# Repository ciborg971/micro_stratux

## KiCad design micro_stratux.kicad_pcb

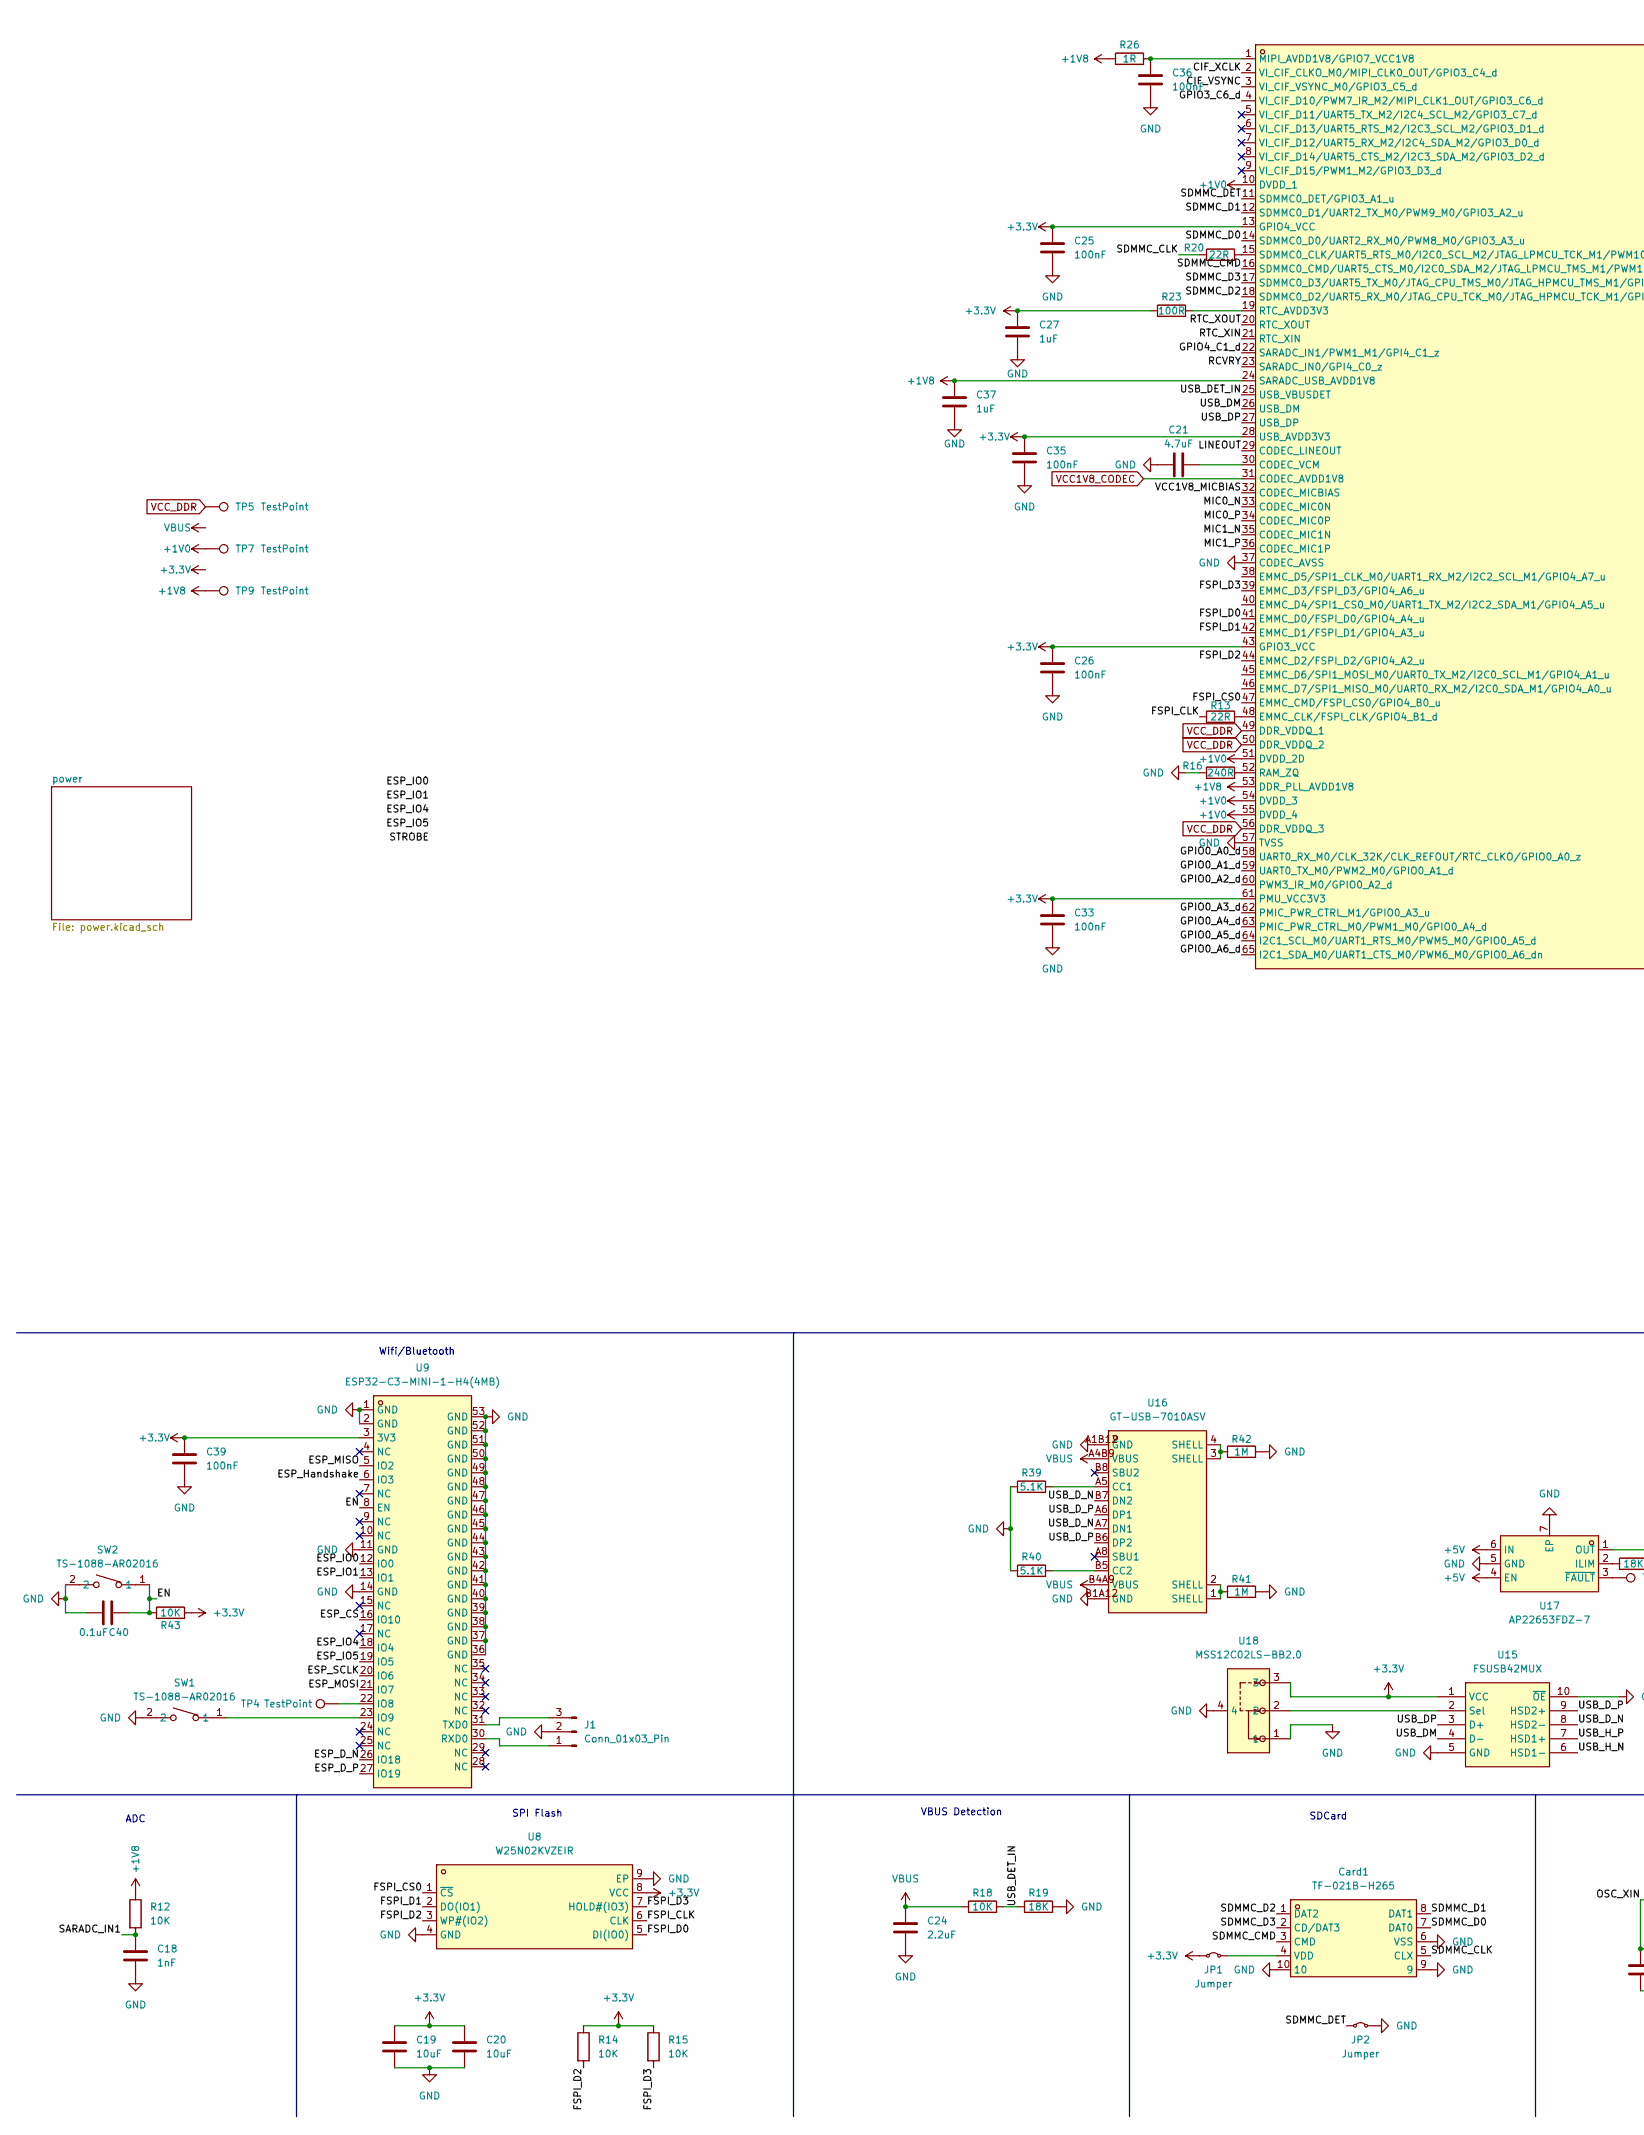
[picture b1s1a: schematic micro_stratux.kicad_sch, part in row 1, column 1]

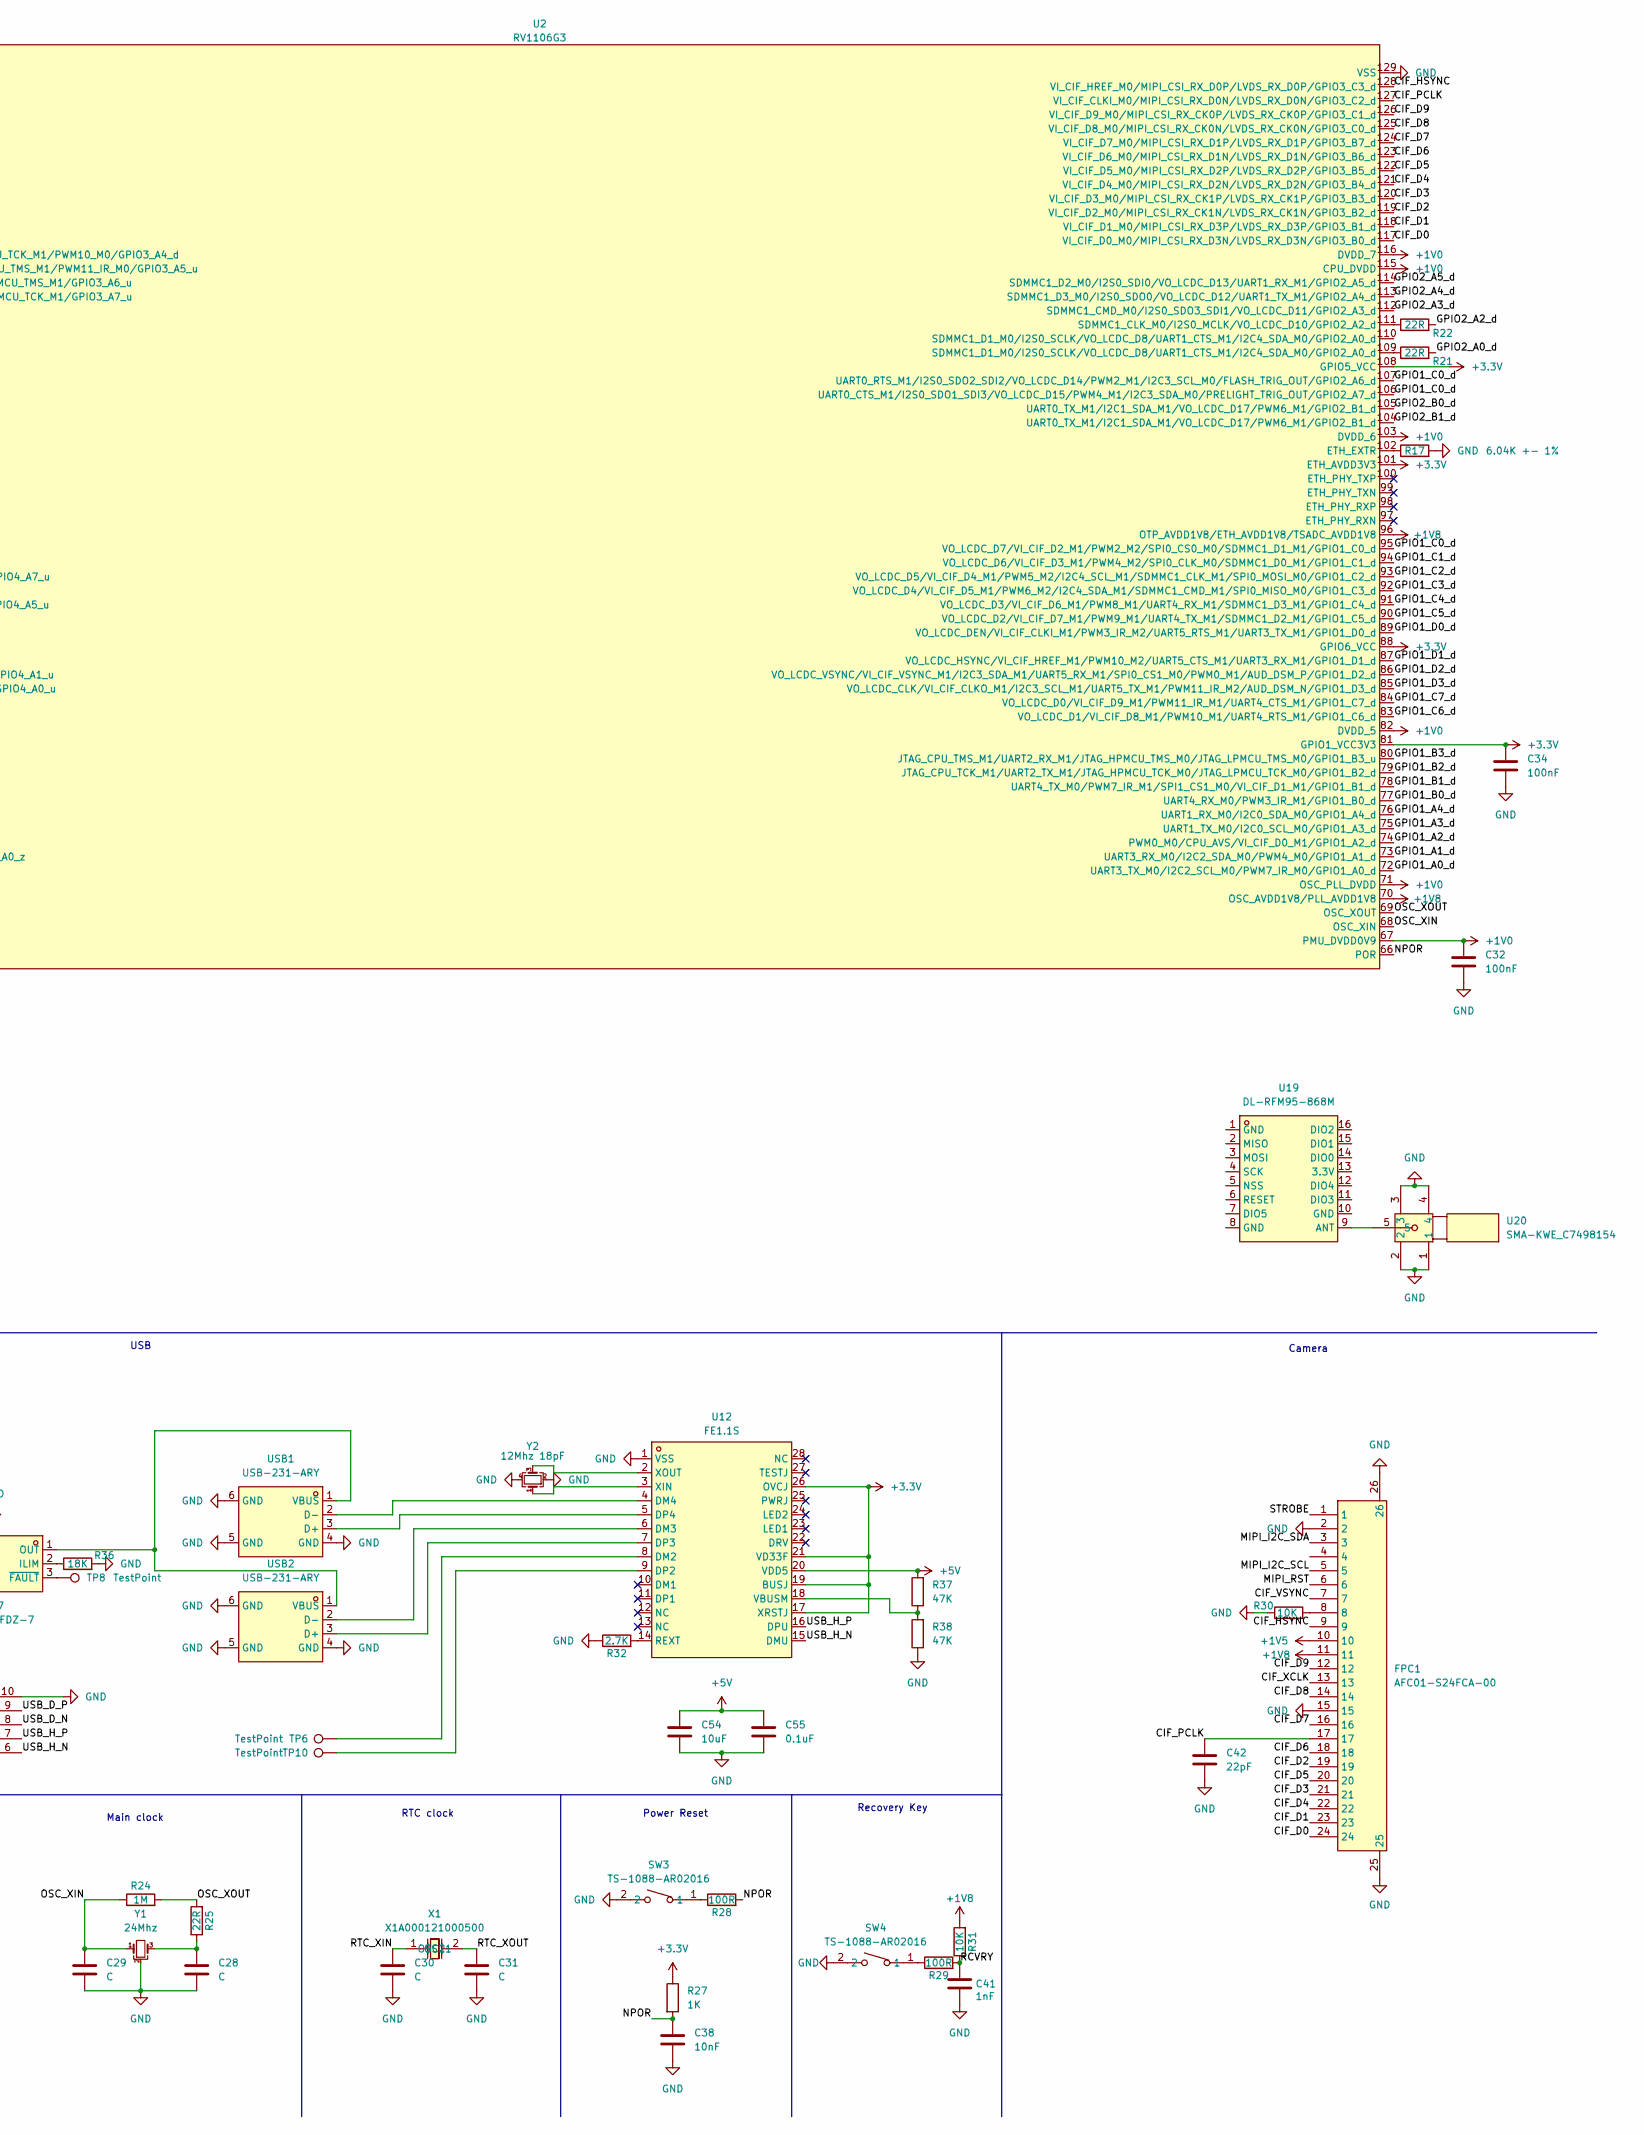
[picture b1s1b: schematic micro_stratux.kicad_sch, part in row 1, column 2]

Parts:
C18, C41: 1nF; C_0402_1005Metric
C19, C20, C54: 10uF; C_0805_2012Metric
C21: 4.7uF; C_0805_2012Metric
C24: 2.2uF; C_0402_1005Metric
C25, C26, C32, C33, C34, C35, C36, C39: 100nF; C_0402_1005Metric
C27, C37: 1uF; C_0402_1005Metric
C28, C29, C30, C31: C; C_0201_0603Metric
C38: 10nF; C_0402_1005Metric
C40, C55: 0.1uF; C_0402_1005Metric
C42: 22pF; C_0201_0603Metric
Card1: TF-021B-H265; TF-SMD_TF-021B-H265; LCSC Part C498185
FPC1: AFC01-S24FCA-00; FPC-SMD_P0.50-24P_FGS-XJ-H2.0; LCSC Part C262669
J1: Conn_01x03_Pin
JP1, JP2: Jumper; TestPoint_2Pads_Pitch2.54mm_Drill0.8mm
R12, R14, R15, R18, R30, R31, R43: 10K; R_0201_0603Metric
R13, R20, R21, R22, R25: 22R; R_0201_0603Metric
R16: 240R; R_0201_0603Metric
R17: 6.04K +- 1%; R_0201_0603Metric
R19: 18K; R_0201_0603Metric
R23, R28, R29: 100R; R_0201_0603Metric
R24, R41, R42: 1M; R_0201_0603Metric
R26: 1R; R_0201_0603Metric
R27: 1K; R_0201_0603Metric
R32: 2.7K; R_0201_0603Metric
R36: 18K; R_0402_1005Metric
R37, R38: 47K; R_0201_0603Metric
R39, R40: 5.1K; R_0201_0603Metric
SW1, SW2, SW3, SW4: TS-1088-AR02016; SW-SMD_L3.9-W3.0-P4.45; LCSC Part C720477
TP4, TP5, TP6, TP7, TP8, TP9, TP10: TestPoint; TestPoint_Pad_D1.0mm
U2: RV1106G3; QFN-128_L12.3-W12.3-P0.35-TL-EP7.0-1; LCSC Part C5328706
U8: W25N02KVZEIR; WSON-8_L8.0-W6.0-P1.27-TL-EP-1; LCSC Part C3010298
U9: ESP32-C3-MINI-1-H4(4MB); WIFIM-SMD_ESP32-C3-MINI-1; LCSC Part C2934569
U12: FE1.1S; SSOP-28_L9.9-W3.9-P0.64-LS6.0-BL-1; LCSC Part C9359
U15: FSUSB42MUX; MSOP-10_L3.0-W3.0-P0.50-LS5.0-BL; LCSC Part C11355
U16: GT-USB-7010ASV; USB-C-SMD_G-SWITCH_GT-USB-7010ASV; LCSC Part C2988369
U17: AP22653FDZ-7; WDFN-6_L2.0-W2.0-P0.65-BL-EP; LCSC Part C3001604
U18: MSS12C02LS-BB2.0; SW-SMD_MSS12C02LS-HB2.0-1; LCSC Part C3008585
U19: DL-RFM95-868M; COMM-SMD_RFM95W; LCSC Part C2844472
U20: SMA-KWE_C7498154; SMA-TH_SMA-KWE_C7498154; LCSC Part C7498154
USB1, USB2: USB-231-ARY; USB-A-TH_USB-231-ARY; LCSC Part C720525
X1: X1A000121000500; CRYSTAL-SMD_L1.7-W1.1; LCSC Part C5154201
Y1: 24Mhz; Crystal_SMD_2016-4Pin_2.0x1.6mm; LCSC C2929397
Y2: 12Mhz 18pF; Crystal_SMD_2520-4Pin_2.5x2.0mm; LCSC C2149207

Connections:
+1V0: C32.1, TP7.1, U2.10 (DVDD_1), U2.51 (DVDD_2D), U2.54 (DVDD_3), U2.55 (DVDD_4), U2.67 (PMU_DVDD0V9), U2.71 (OSC_PLL_DVDD), U2.82 (DVDD_5), U2.103 (DVDD_6), U2.115 (CPU_DVDD), U2.116 (DVDD_7); also elsewhere on the board
+1V5: FPC1.10; also elsewhere on the board
+1V8: C37.1, FPC1.11, R12.1, R26.1, R31.2, TP9.1, U2.24 (SARADC_USB_AVDD1V8), U2.53 (DDR_PLL_AVDD1V8), U2.70 (OSC_AVDD1V8/PLL_AVDD1V8), U2.96 (OTP_AVDD1V8/ETH_AVDD1V8/TSADC_AVDD1V8); also elsewhere on the board
+3.3V: C19.1, C20.1, C25.1, C26.1, C27.1, C33.1, C34.1, C35.1, C39.1, JP1.1 (A), R14.1, R15.1, R23.1, R27.1, R43.2, U2.13 (GPIO4_VCC), U2.28 (USB_AVDD3V3), U2.43 (GPIO3_VCC), U2.61 (PMU_VCC3V3), U2.81 (GPIO1_VCC3V3), U2.88 (GPIO6_VCC), U2.101 (ETH_AVDD3V3), U2.108 (GPIO5_VCC), U8.8 (VCC), U9.3 (3V3), U12.17 (XRSTJ), U12.19 (BUSJ), U12.21 (VD33F), U12.26 (OVCJ), U15.1 (VCC), U18.3; also elsewhere on the board
+5V: C54.1, C55.1, R37.2, U12.20 (VDD5), U17.4 (EN), U17.6 (IN); also elsewhere on the board
/CIF_D0: FPC1.24, U2.117 (VI_CIF_D0_M0/MIPI_CSI_RX_D3N/LVDS_RX_D3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)
/CIF_D1: FPC1.23, U2.118 (VI_CIF_D1_M0/MIPI_CSI_RX_D3P/LVDS_RX_D3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)
/CIF_D2: FPC1.19, U2.119 (VI_CIF_D2_M0/MIPI_CSI_RX_CK1N/LVDS_RX_C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)
/CIF_D3: FPC1.21, U2.120 (VI_CIF_D3_M0/MIPI_CSI_RX_CK1P/LVDS_RX_C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)
/CIF_D4: FPC1.22, U2.121 (VI_CIF_D4_M0/MIPI_CSI_RX_D2N/LVDS_RX_D2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)
/CIF_D5: FPC1.20, U2.122 (VI_CIF_D5_M0/MIPI_CSI_RX_D2P/LVDS_RX_D2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)
/CIF_D6: FPC1.18, U2.123 (VI_CIF_D6_M0/MIPI_CSI_RX_D1N/LVDS_RX_D1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)
/CIF_D7: FPC1.16, U2.124 (VI_CIF_D7_M0/MIPI_CSI_RX_D1P/LVDS_RX_D1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)
/CIF_D8: FPC1.14, U2.125 (VI_CIF_D8_M0/MIPI_CSI_RX_CK0N/LVDS_RX_C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)
/CIF_D9: FPC1.12, U2.126 (VI_CIF_D9_M0/MIPI_CSI_RX_CK0P/LVDS_RX_C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)
/CIF_HSYNC: FPC1.9, U2.128 (VI_CIF_HREF_M0/MIPI_CSI_RX_D0P/LVDS_RX_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)
/CIF_PCLK: C42.1, FPC1.17, U2.127 (VI_CIF_CLKI_M0/MIPI_CSI_RX_D0N/LVDS_RX_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)
/CIF_VSYNC: FPC1.7, U2.3 (VI_CIF_VSYNC_M0/GPIO3_C5_d)
/CIF_XCLK: FPC1.13, U2.2 (VI_CIF_CLKO_M0/MIPI_CLK0_OUT/GPIO3_C4_d)
/EN: C40.2, R43.1, SW2.1, U9.8 (EN)
/ESP_CS: U9.16 (IO10)
/ESP_D_N: U9.26 (IO18)
/ESP_D_P: U9.27 (IO19)
/ESP_Handshake: U9.6 (IO3)
/ESP_IO0: U9.12 (IO0)
/ESP_IO1: U9.13 (IO1)
/ESP_IO4: U9.18 (IO4)
/ESP_IO5: U9.19 (IO5)
/ESP_MISO: U9.5 (IO2)
/ESP_MOSI: U9.21 (IO7)
/ESP_SCLK: U9.20 (IO6)
/FSPI_CLK: R13.1, U8.6 (CLK)
/FSPI_CS0: U2.47 (EMMC_CMD/FSPI_CS0/GPIO4_B0_u), U8.1 (~CS)
/FSPI_D0: U2.41 (EMMC_D0/FSPI_D0/GPIO4_A4_u), U8.5 (DI(IO0))
/FSPI_D1: U2.42 (EMMC_D1/FSPI_D1/GPIO4_A3_u), U8.2 (DO(IO1))
/FSPI_D2: R14.2, U2.44 (EMMC_D2/FSPI_D2/GPIO4_A2_u), U8.3 (WP#(IO2))
/FSPI_D3: R15.2, U2.39 (EMMC_D3/FSPI_D3/GPIO4_A6_u), U8.7 (HOLD#(IO3))
/GPIO0_A0_d: U2.58 (UART0_RX_M0/CLK_32K/CLK_REFOUT/RTC_CLKO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)
/GPIO0_A1_d: U2.59 (UART0_TX_M0/PWM2_M0/GPIO0_A1_d)
/GPIO0_A2_d: U2.60 (PWM3_IR_M0/GPIO0_A2_d)
/GPIO0_A3_d: U2.62 (PMIC_PWR_CTRL_M1/GPIO0_A3_u)
/GPIO0_A4_d: U2.63 (PMIC_PWR_CTRL_M0/PWM1_M0/GPIO0_A4_d)
/GPIO0_A5_d: U2.64 (I2C1_SCL_M0/UART1_RTS_M0/PWM5_M0/GPIO0_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)
/GPIO0_A6_d: U2.65 (I2C1_SDA_M0/UART1_CTS_M0/PWM6_M0/GPIO0_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)
/GPIO1_A0_d: U2.72 (UART3_TX_M0/I2C2_SCL_M0/PWM7_IR_M0/GPIO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)
/GPIO1_A1_d: U2.73 (UART3_RX_M0/I2C2_SDA_M0/PWM4_M0/GPIO1_A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)
/GPIO1_A2_d: U2.74 (PWM0_M0/CPU_AVS/VI_CIF_D0_M1/GPIO1_A2_d)
/GPIO1_A3_d: U2.75 (UART1_TX_M0/I2C0_SCL_M0/GPIO1_A3_d)
/GPIO1_A4_d: U2.76 (UART1_RX_M0/I2C0_SDA_M0/GPIO1_A4_d)
/GPIO1_B0_d: U2.77 (UART4_RX_M0/PWM3_IR_M1/GPIO1_B0_d)
/GPIO1_B1_d: U2.78 (UART4_TX_M0/PWM7_IR_M1/SPI1_CS1_M0/VI_C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)
/GPIO1_B2_d: U2.79 (JTAG_CPU_TCK_M1/UART2_TX_M1/JTAG_HPMCU_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)
/GPIO1_B3_d: U2.80 (JTAG_CPU_TMS_M1/UART2_RX_M1/JTAG_HPMCU_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)
/GPIO1_C0_d: U2.95 (VO_LCDC_D7/VI_CIF_D2_M1/PWM2_M2/SPI0_CS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), U2.106 (UART0_CTS_M1/I2S0_SDO1_SDI3/VO_LCDC_D15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), U2.107 (UART0_RTS_M1/I2S0_SDO2_SDI2/VO_LCDC_D14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)
/GPIO1_C1_d: U2.94 (VO_LCDC_D6/VI_CIF_D3_M1/PWM4_M2/SPI0_CL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)
/GPIO1_C2_d: U2.93 (VO_LCDC_D5/VI_CIF_D4_M1/PWM5_M2/I2C4_SC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)
/GPIO1_C3_d: U2.92 (VO_LCDC_D4/VI_CIF_D5_M1/PWM6_M2/I2C4_SD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)
/GPIO1_C4_d: U2.91 (VO_LCDC_D3/VI_CIF_D6_M1/PWM8_M1/UART4_R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)
/GPIO1_C5_d: U2.90 (VO_LCDC_D2/VI_CIF_D7_M1/PWM9_M1/UART4_T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)
/GPIO1_C6_d: U2.83 (VO_LCDC_D1/VI_CIF_D8_M1/PWM10_M1/UART4_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)
/GPIO1_C7_d: U2.84 (VO_LCDC_D0/VI_CIF_D9_M1/PWM11_IR_M1/UAR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)
/GPIO1_D0_d: U2.89 (VO_LCDC_DEN/VI_CIF_CLKI_M1/PWM3_IR_M2/U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)
/GPIO1_D1_d: U2.87 (VO_LCDC_HSYNC/VI_CIF_HREF_M1/PWM10_M2/U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)
/GPIO1_D2_d: U2.86 (VO_LCDC_VSYNC/VI_CIF_VSYNC_M1/I2C3_SDA_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)
/GPIO1_D3_d: U2.85 (VO_LCDC_CLK/VI_CIF_CLKO_M1/I2C3_SCL_M1/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)
/GPIO2_A0_d: R21.2
/GPIO2_A2_d: R22.2
/GPIO2_A3_d: U2.112 (SDMMC1_CMD_M0/I2S0_SDO3_SDI1/VO_LCDC_D1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)
/GPIO2_A4_d: U2.113 (SDMMC1_D3_M0/I2S0_SDO0/VO_LCDC_D12/UART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)
/GPIO2_A5_d: U2.114 (SDMMC1_D2_M0/I2S0_SDI0/VO_LCDC_D13/UART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)
/GPIO2_B0_d: U2.105 (UART0_TX_M1/I2C1_SDA_M1/VO_LCDC_D17/PWM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)
/GPIO2_B1_d: U2.104 (UART0_TX_M1/I2C1_SDA_M1/VO_LCDC_D17/PWM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)
/GPIO3_C6_d: U2.4 (VI_CIF_D10/PWM7_IR_M2/MIPI_CLK1_OUT/GPI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)
/GPIO4_C1_d: U2.22 (SARADC_IN1/PWM1_M1/GPI4_C1_z)
/LINEOUT: U2.29 (CODEC_LINEOUT)
/MIC0_N: U2.33 (CODEC_MIC0N)
/MIC0_P: U2.34 (CODEC_MIC0P)
/MIC1_N: U2.35 (CODEC_MIC1N)
/MIC1_P: U2.36 (CODEC_MIC1P)
/MIPI_I2C_SCL: FPC1.5
/MIPI_I2C_SDA: FPC1.3
/MIPI_RST: FPC1.6
/NPOR: C38.1, R27.2, R28.2, U2.66 (POR)
/OSC_XIN: C29.1, R24.1, U2.68 (OSC_XIN), Y1.1
/OSC_XOUT: R24.2, R25.2, U2.69 (OSC_XOUT)
/RCVRY: C41.1, R29.2, R31.1, U2.23 (SARADC_IN0/GPI4_C0_z)
/RTC_XIN: C30.1, U2.21 (RTC_XIN), X1.1 (OSC1)
/RTC_XOUT: C31.1, U2.20 (RTC_XOUT), X1.2 (OSC2)
/SARADC_IN1: C18.1, R12.2
/SDMMC_CLK: Card1.5 (CLX), R20.1
/SDMMC_CMD: Card1.3 (CMD), U2.16 (SDMMC0_CMD/UART5_CTS_M0/I2C0_SDA_M2/JTA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)
/SDMMC_D0: Card1.7 (DAT0), U2.14 (SDMMC0_D0/UART2_RX_M0/PWM8_M0/GPIO3_A3_u)
/SDMMC_D1: Card1.8 (DAT1), U2.12 (SDMMC0_D1/UART2_TX_M0/PWM9_M0/GPIO3_A2_u)
/SDMMC_D2: Card1.1 (DAT2), U2.18 (SDMMC0_D2/UART5_RX_M0/JTAG_CPU_TCK_M0/J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)
/SDMMC_D3: Card1.2 (CD/DAT3), U2.17 (SDMMC0_D3/UART5_TX_M0/JTAG_CPU_TMS_M0/J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)
/SDMMC_DET: JP2.1 (A), U2.11 (SDMMC0_DET/GPIO3_A1_u)
/STROBE: FPC1.1
/USB_DET_IN: R18.2, R19.1, U2.25 (USB_VBUSDET)
/USB_DM: U2.26 (USB_DM), U15.4 (D-)
/USB_DP: U2.27 (USB_DP), U15.3 (D+)
/USB_D_N: U15.8 (HSD2-), U16.A7 (DN1), U16.B7 (DN2)
/USB_D_P: U15.9 (HSD2+), U16.A6 (DP1), U16.B6 (DP2)
/USB_H_N: U12.15 (DMU), U15.6 (HSD1-)
/USB_H_P: U12.16 (DPU), U15.7 (HSD1+)
/VCC1V8_MICBIAS: U2.32 (CODEC_MICBIAS)
GND: C18.2, C19.2, C20.2, C21.1, C24.2, C25.2, C26.2, C27.2, C28.2, C29.2, C30.2, C31.2, C32.2, C33.2, C34.2, C35.2, C36.2, C37.2, C38.2, C39.2, C40.1, C41.2, C42.2, C54.2, C55.2, Card1.6 (VSS), Card1.9, Card1.10, FPC1.2, FPC1.15, FPC1.25, FPC1.26, J1.2, JP2.2 (B), R16.1, R17.2, R19.2, R30.1, R32.1, R36.2, R38.1, R39.1, R40.1, R41.2, R42.2, SW1.2, SW2.2, SW3.2, SW4.2, U2.37 (CODEC_AVSS), U2.57 (TVSS), U2.129 (VSS), U8.4 (GND), U8.9 (EP), U9.1 (GND), U9.2 (GND), U9.11 (GND), U9.14 (GND), U9.36 (GND), U9.37 (GND), U9.38 (GND), U9.39 (GND), U9.40 (GND), U9.41 (GND), U9.42 (GND), U9.43 (GND), U9.44 (GND), U9.45 (GND), U9.46 (GND), U9.47 (GND), U9.48 (GND), U9.49 (GND), U9.50 (GND), U9.51 (GND), U9.52 (GND), U9.53 (GND), U12.1 (VSS), U15.5 (GND), U15.10 (~OE), U16.A1B12 (GND), U16.B1A12 (GND), U17.5 (GND), U17.7 (EP), U18.1, U18.4, U20.1, U20.2, U20.3, U20.4, USB1.4 (GND), USB1.5 (GND), USB1.6 (GND), USB2.4 (GND), USB2.5 (GND), USB2.6 (GND), Y1.2, Y2.2, Y2.4; also elsewhere on the board
unnamed: C28.1, R25.1, Y1.3
unnamed: Card1.4 (VDD), JP1.2 (B)
unnamed: FPC1.8, R30.2
unnamed: J1.1, U9.30 (RXD0)
unnamed: J1.3, U9.31 (TXD0)
unnamed: R21.1, U2.109 (SDMMC1_D1_M0/I2S0_SCLK/VO_LCDC_D8/UART1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)
unnamed: R28.1, SW3.1
unnamed: R29.1, SW4.1
unnamed: R41.1, U16.1 (SHELL), U16.2 (SHELL)
unnamed: R42.1, U16.3 (SHELL), U16.4 (SHELL)
unnamed: C21.2, U2.30 (CODEC_VCM)
unnamed: R13.2, U2.48 (EMMC_CLK/FSPI_CLK/GPIO4_B1_d)
unnamed: R17.1, U2.102 (ETH_EXTR)
unnamed: C36.1, R26.2, U2.1 (MIPI_AVDD1V8/GPIO7_VCC1V8)
unnamed: R16.2, U2.52 (RAM_ZQ)
unnamed: R23.2, U2.19 (RTC_AVDD3V3)
unnamed: R20.2, U2.15 (SDMMC0_CLK/UART5_RTS_M0/I2C0_SCL_M2/JTA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)
unnamed: R22.1, U2.111 (SDMMC1_CLK_M0/I2S0_MCLK/VO_LCDC_D10/GPI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)
unnamed: TP4.1, U9.22 (IO8)
unnamed: SW1.1, U9.23 (IO9)
unnamed: TP6.1, U12.8 (DM2)
unnamed: U12.6 (DM3), USB2.2 (D-)
unnamed: U12.4 (DM4), USB1.2 (D-)
unnamed: TP10.1, U12.9 (DP2)
unnamed: U12.7 (DP3), USB2.3 (D+)
unnamed: U12.5 (DP4), USB1.3 (D+)
unnamed: R32.2, U12.14 (REXT)
unnamed: R37.1, R38.2, U12.18 (VBUSM)
unnamed: U12.3 (XIN), Y2.1
unnamed: U12.2 (XOUT), Y2.3
unnamed: U15.2 (Sel), U18.2
unnamed: R39.2, U16.A5 (CC1)
unnamed: R40.2, U16.B5 (CC2)
unnamed: R36.1, U17.2 (ILIM)
unnamed: U17.1 (OUT), USB1.1 (VBUS), USB2.1 (VBUS)
unnamed: TP8.1, U17.3 (~FAULT)
unnamed: U19.9 (ANT), U20.5
VBUS: C24.1, R18.1, U16.A4B9 (VBUS), U16.B4A9 (VBUS); also elsewhere on the board
VCC1V8_CODEC: U2.31 (CODEC_AVDD1V8); also elsewhere on the board
VCC_DDR: TP5.1, U2.49 (DDR_VDDQ_1), U2.50 (DDR_VDDQ_2), U2.56 (DDR_VDDQ_3); also elsewhere on the board

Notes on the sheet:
SPI Flash
Camera
RTC clock
VBUS Detection
Recovery Key
Power Reset
SDCard
ADC
USB
Wifi/Bluetooth
Main clock

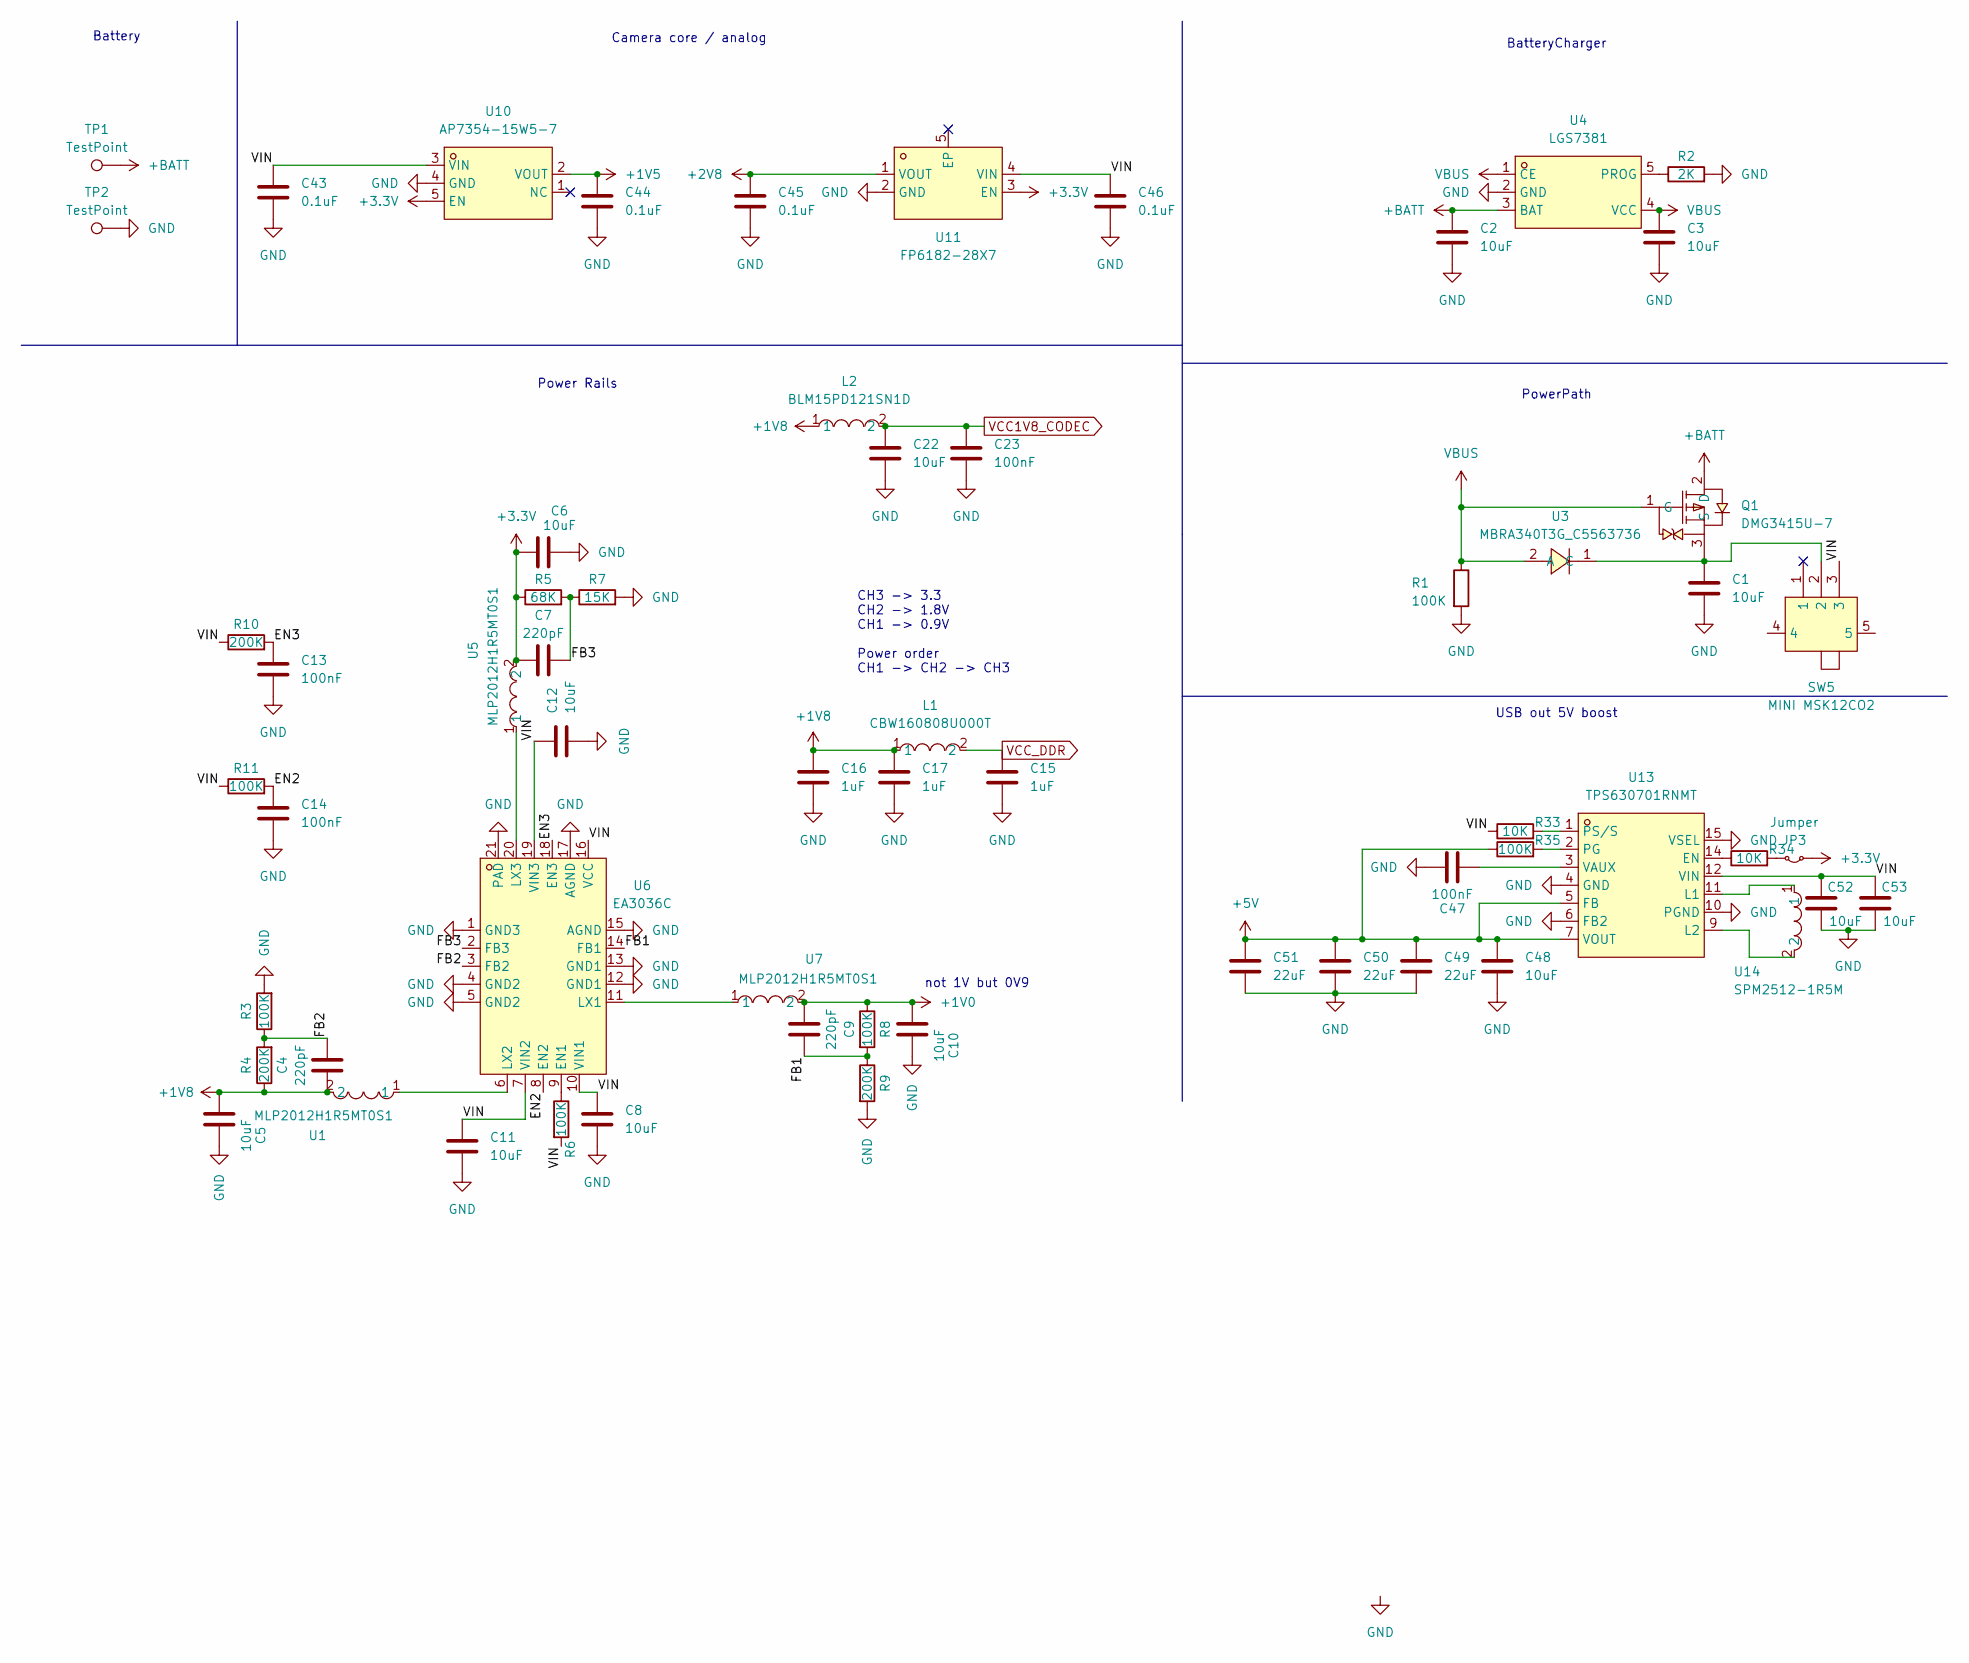
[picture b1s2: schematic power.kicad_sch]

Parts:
C1, C2, C3, C5, C6, C8, C10, C11, C12, C22, C48, C52, C53: 10uF; C_0805_2012Metric
C4, C7, C9: 220pF; C_0201_0603Metric
C13, C14, C23, C47: 100nF; C_0402_1005Metric
C15, C16, C17: 1uF; C_0402_1005Metric
C43, C44, C45, C46: 0.1uF; C_0402_1005Metric
C49, C50, C51: 22uF; C_0805_2012Metric
JP3: Jumper; TestPoint_2Pads_Pitch2.54mm_Drill0.8mm
L1: CBW160808U000T; L0603; LCSC Part C139173
L2: BLM15PD121SN1D; L0402; LCSC Part C76891
Q1: DMG3415U-7; SOT-23-3_L2.9-W1.6-P1.90-LS2.8-BR-CW; LCSC Part C96616
R1: 100K; R_0402_1005Metric
R2: 2K; R_0402_1005Metric
R3, R6, R8, R11, R35: 100K; R_0201_0603Metric
R4, R9, R10: 200K; R_0201_0603Metric
R5: 68K; R_0201_0603Metric
R7: 15K; R_0201_0603Metric
R33, R34: 10K; R_0201_0603Metric
SW5: MINI MSK12CO2; SW-SMD_MSK12CO2; LCSC Part C2681570
TP1, TP2: TestPoint; TestPoint_Pad_D1.0mm
U1, U5, U7: MLP2012H1R5MT0S1; L0805; LCSC Part C2042639
U3: MBRA340T3G_C5563736; SMA_L4.5-W2.6-LS5.2-RD; LCSC Part C5563736
U4: LGS7381; SOT-23-5_L2.9-W1.6-P0.95-LS2.8-BR; LCSC Part C5299900
U6: EA3036C; WQFN-20_L3.0-W3.0-P0.40-BL-EP; LCSC Part C570857
U10: AP7354-15W5-7; SOT-25_L2.9-W1.6-P0.95-LS2.8-BL; LCSC Part C460385
U11: FP6182-28X7; UTDFN-4_L1.0-W1.0-P0.63-BL-EP; LCSC Part C498349
U13: TPS630701RNMT; VQFN-15_L3.0-W2.5-P0.50-BL; LCSC Part C181473
U14: SPM2512-1R5M; IND-SMD_L2.5-W2.0_MHCHL2520; LCSC Part C2761859

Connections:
+1V0: C9.1, C10.1, R8.1, U7.2; also elsewhere on the board
+1V5: C44.1, U10.2 (VOUT); also elsewhere on the board
+1V8: C4.1, C5.1, C16.1, C17.1, L1.1, L2.1, R4.1, U1.2; also elsewhere on the board
+2V8: C45.1, U11.1 (VOUT)
+3.3V: C6.1, C7.1, JP3.1 (A), R5.1, U5.2, U10.5 (EN), U11.3 (EN); also elsewhere on the board
+5V: C48.1, C49.1, C50.1, C51.1, R35.1, U13.5 (FB), U13.7 (VOUT); also elsewhere on the board
+BATT: C2.1, Q1.2 (D), TP1.1, U4.3 (BAT)
/power/EN2: C14.1, R11.2, U6.8 (EN2)
/power/EN3: C13.1, R10.2, U6.18 (EN3)
/power/FB1: C9.2, R8.2, R9.1, U6.14 (FB1)
/power/FB2: C4.2, R3.1, R4.2, U6.3 (FB2)
/power/FB3: C7.2, R5.2, R7.1, U6.2 (FB3)
/power/VIN: C8.1, C11.1, C12.1, C43.1, C46.1, C52.1, C53.1, R6.2, R10.1, R11.1, R33.1, SW5.3, U6.7 (VIN2), U6.10 (VIN1), U6.16 (VCC), U6.19 (VIN3), U10.3 (VIN), U11.4 (VIN), U13.12 (VIN)
GND: C1.2, C2.2, C3.2, C5.2, C6.2, C8.2, C10.2, C11.2, C12.2, C13.2, C14.2, C15.2, C16.2, C17.2, C22.2, C23.2, C43.2, C44.2, C45.2, C46.2, C47.1, C48.2, C49.2, C50.2, C51.2, C52.2, C53.2, R1.2, R2.2, R3.2, R7.2, R9.2, TP2.1, U4.2 (GND), U6.1 (GND3), U6.4 (GND2), U6.5 (GND2), U6.12 (GND1), U6.13 (GND1), U6.15 (AGND), U6.17 (AGND), U6.21 (PAD), U10.4 (GND), U11.2 (GND), U13.4 (GND), U13.6 (FB2), U13.10 (PGND), U13.15 (VSEL); also elsewhere on the board
unnamed: JP3.2 (B), R34.2
unnamed: C1.1, Q1.3 (S), SW5.2, U3.1 (C)
unnamed: R2.1, U4.5 (PROG)
unnamed: R6.1, U6.9 (EN1)
unnamed: U6.11 (LX1), U7.1
unnamed: U1.1, U6.6 (LX2)
unnamed: U5.1, U6.20 (LX3)
unnamed: R34.1, U13.14 (EN)
unnamed: U13.11 (L1), U14.1
unnamed: U13.9 (L2), U14.2
unnamed: R35.2, U13.2 (PG)
unnamed: R33.2, U13.1 (PS/S)
unnamed: C47.2, U13.3 (VAUX)
VBUS: C3.1, Q1.1 (G), R1.1, U3.2 (A), U4.1 (CE), U4.4 (VCC); also elsewhere on the board
VCC1V8_CODEC: C22.1, C23.1, L2.2; also elsewhere on the board
VCC_DDR: C15.1, L1.2; also elsewhere on the board

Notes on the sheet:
CH3 -> 3.3 CH2 -> 1.8V CH1 -> 0.9V Power order CH1 -> CH2 -> CH3
USB out 5V boost
BatteryCharger
PowerPath
not 1V but 0V9
Power Rails
Battery
Camera core / analog

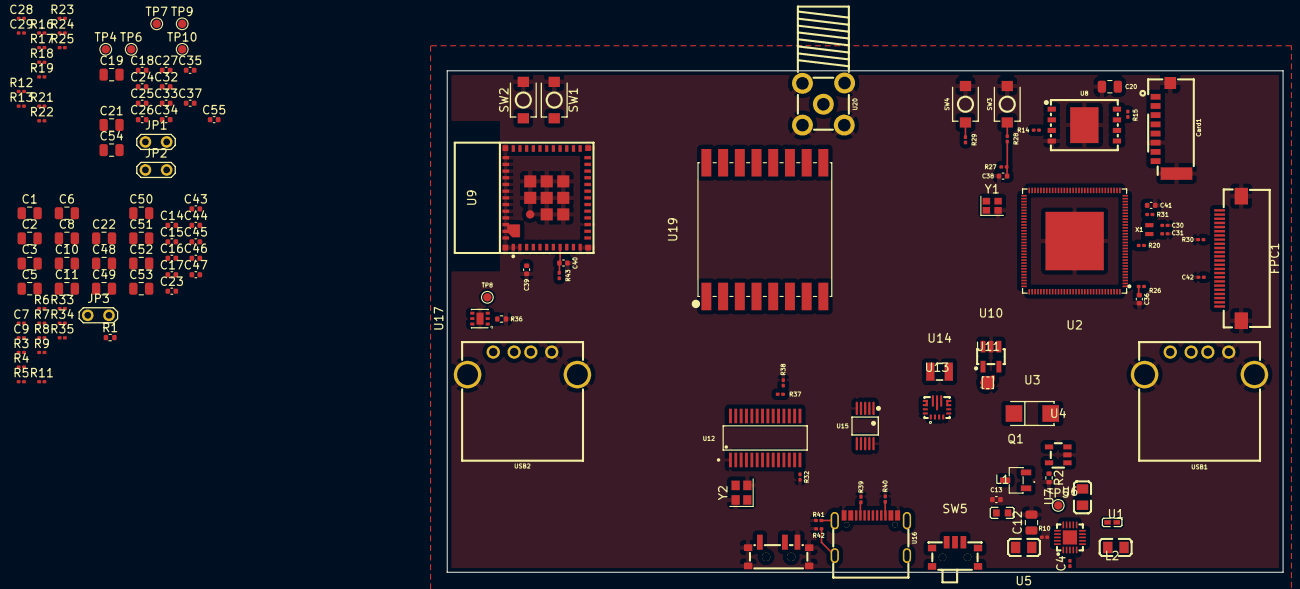
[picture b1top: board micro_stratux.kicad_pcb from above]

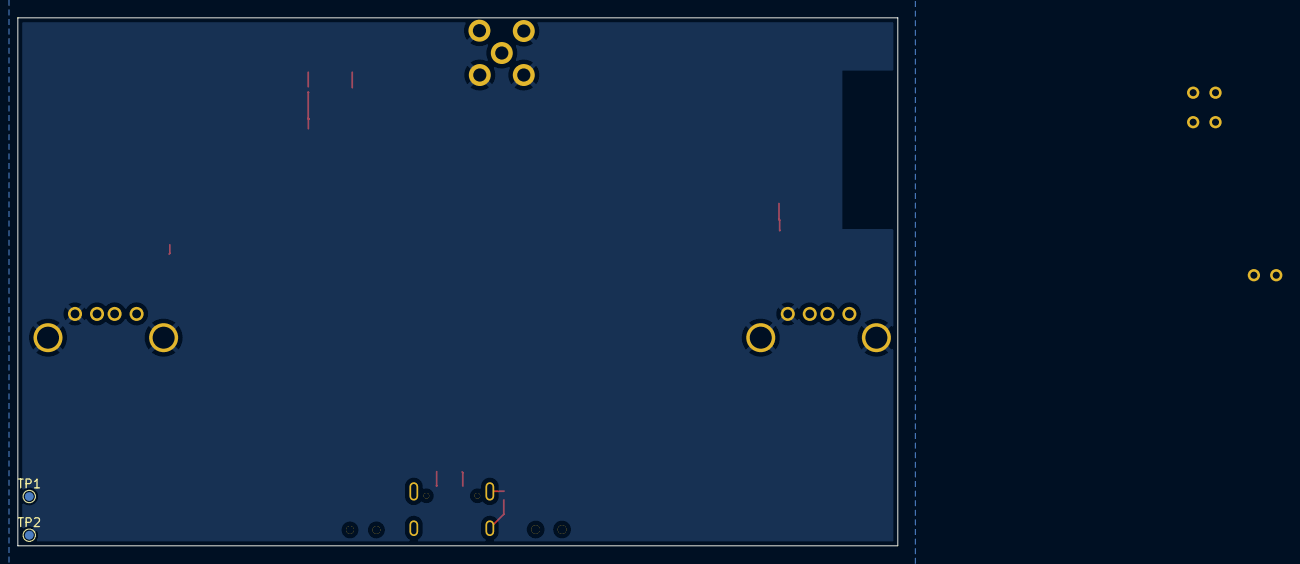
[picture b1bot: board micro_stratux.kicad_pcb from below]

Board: 4 copper layers, 100.0 x 60.0 mm, 145 parts (2 on the bottom side), 108 nets.

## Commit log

2024-10-18 add all files
